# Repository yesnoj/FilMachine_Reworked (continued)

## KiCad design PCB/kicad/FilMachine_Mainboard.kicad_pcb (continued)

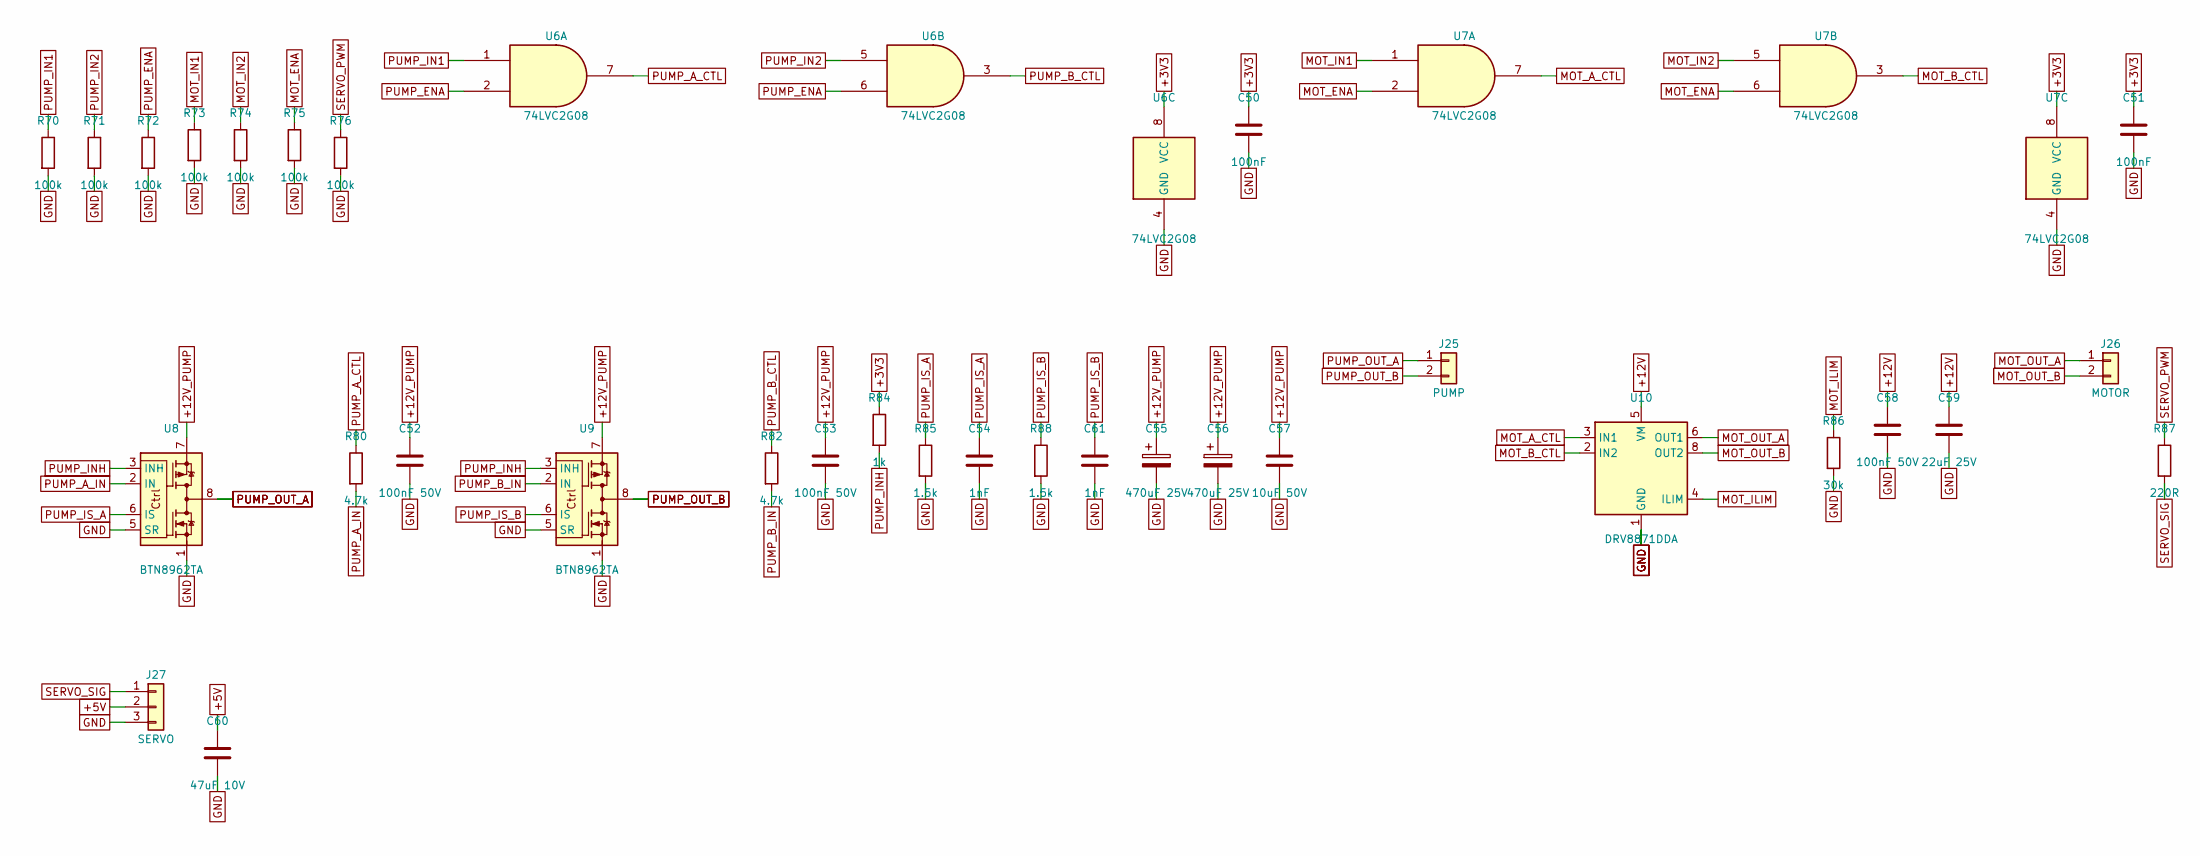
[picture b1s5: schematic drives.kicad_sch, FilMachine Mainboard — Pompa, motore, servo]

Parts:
C50, C51: 100nF; C_0603_1608Metric; MPN MLCC 100nF; LCSC C14663
C52, C53, C58: 100nF 50V; C_0805_2012Metric; MPN MLCC 100nF 50V; LCSC C49678
C54, C61: 1nF; C_0603_1608Metric; MPN MLCC 1nF; LCSC C1588
C55, C56: 470uF 25V; CP_Radial_D10.0mm_P5.00mm; MPN 25ZLH470MEFC10X12.5; LCSC C338188
C57: 10uF 50V; C_1206_3216Metric; MPN MLCC 10uF 50V; LCSC C13585
C59: 22uF 25V; C_1206_3216Metric; MPN MLCC 22uF 25V; LCSC C12891
C60: 47uF 10V; C_1206_3216Metric; MPN MLCC 47uF 10V; LCSC C96123
J25: PUMP; TB_WJ500V-5.08-2P; MPN WJ500V-5.08-2P; LCSC C8465
J26: MOTOR; TB_DB301V-3.5-2P; MPN DB301V-3.5-2P-GN-S; LCSC C695629
J27: SERVO; PinHeader_1x03_P2.54mm_Vertical; MPN PZ254V-11-03P; LCSC C2937625
R70, R71, R72, R73, R74, R75, R76: 100k; R_0603_1608Metric; MPN 0603 100k 1%; LCSC C25803
R80, R82: 4.7k; R_0603_1608Metric; MPN 0603 4.7k 1%; LCSC C23162
R84: 1k; R_0603_1608Metric; MPN 0603 1k 1%; LCSC C21190
R85, R88: 1.5k; R_0603_1608Metric; MPN 0603 1.5k 1%; LCSC C22843
R86: 30k; R_0603_1608Metric; MPN 0603 30k 1%; LCSC C22984
R87: 220R; R_0603_1608Metric; MPN 0603 220R 1%; LCSC C22962
U6, U7: 74LVC2G08; SSOP-8_2.95x2.8mm_P0.65mm; MPN SN74LVC2G08DCTR; LCSC C352973
U8, U9: BTN8962TA; TO-263-7_TabPin8; MPN BTN8962TAAUMA1; LCSC C112630
U10: DRV8871DDA; TI_SO-PowerPAD-8_ThermalVias; MPN DRV8871DDAR; LCSC C75864

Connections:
+3V3: C50.1, C51.1, R84.1, U6.8 (VCC), U7.8 (VCC); also elsewhere on the board
+5V: C60.1, J27.2; also elsewhere on the board
+12V: C58.1, C59.1, U10.5 (VM); also elsewhere on the board
+12V_PUMP: C52.1, C53.1, C55.1, C56.1, C57.1, U8.7, U9.7; also elsewhere on the board
GND: C50.2, C51.2, C52.2, C53.2, C54.2, C55.2, C56.2, C57.2, C58.2, C59.2, C60.2, C61.2, J27.3, R70.2, R71.2, R72.2, R73.2, R74.2, R75.2, R76.2, R85.2, R86.2, R88.2, U6.4 (GND), U7.4 (GND), U8.1, U8.5 (SR), U9.1, U9.5 (SR), U10.1 (GND), U10.7 (GND), U10.9 (GND); also elsewhere on the board
MOT_A_CTL: U7.7, U10.3 (IN1)
MOT_B_CTL: U7.3, U10.2 (IN2)
MOT_ENA: R75.1, U7.2, U7.6; also elsewhere on the board
MOT_ILIM: R86.1, U10.4 (ILIM)
MOT_IN1: R73.1, U7.1; also elsewhere on the board
MOT_IN2: R74.1, U7.5; also elsewhere on the board
MOT_OUT_A: J26.1, U10.6 (OUT1)
MOT_OUT_B: J26.2, U10.8 (OUT2)
PUMP_A_CTL: R80.1, U6.7
PUMP_A_IN: R80.2, U8.2 (IN)
PUMP_B_CTL: R82.1, U6.3
PUMP_B_IN: R82.2, U9.2 (IN)
PUMP_ENA: R72.1, U6.2, U6.6; also elsewhere on the board
PUMP_IN1: R70.1, U6.1; also elsewhere on the board
PUMP_IN2: R71.1, U6.5; also elsewhere on the board
PUMP_INH: R84.2, U8.3 (INH), U9.3 (INH)
PUMP_IS_A: C54.1, R85.1, U8.6 (IS); also elsewhere on the board
PUMP_IS_B: C61.1, R88.1, U9.6 (IS); also elsewhere on the board
PUMP_OUT_A: J25.1, U8.4, U8.8
PUMP_OUT_B: J25.2, U9.4, U9.8
SERVO_PWM: R76.1, R87.1; also elsewhere on the board
SERVO_SIG: J27.1, R87.2

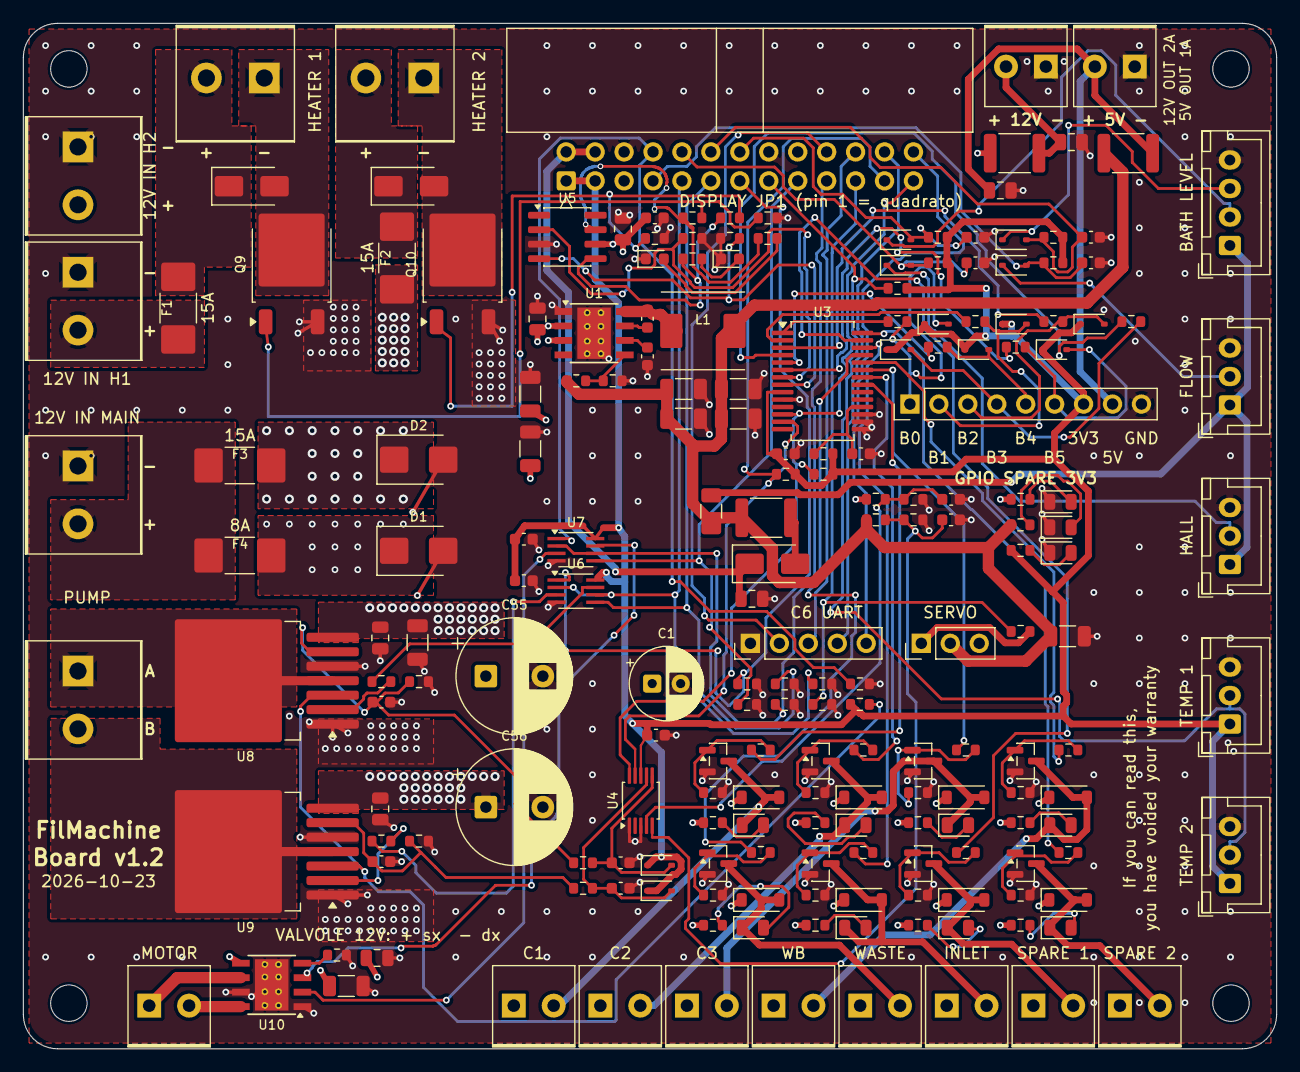
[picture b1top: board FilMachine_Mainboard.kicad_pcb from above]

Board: 4 copper layers, 110.0 x 90.0 mm, 205 parts (0 on the bottom side), 118 nets.

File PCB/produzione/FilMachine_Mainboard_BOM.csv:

Comment,Designator,Footprint,LCSC Part #
100uF 35V,C1,CP_Radial_D6.3mm_P2.50mm,C106694
10uF 50V,"C2,C3,C57",C_1206_3216Metric,C13585
220nF 50V,C4,C_0805_2012Metric,C5378
100nF,"C5,C13,C14,C15,C16,C17,C18,C19,C41,C50,C51",C_0603_1608Metric,C14663
1uF 50V,C6,C_0603_1608Metric,C15849
22uF 25V,"C7,C8,C9,C10,C59",C_1206_3216Metric,C12891
1nF,"C20,C21,C22,C23,C54,C61",C_0603_1608Metric,C1588
1uF 50V,C40,C_0805_2012Metric,C28323
100nF 50V,"C52,C53,C58",C_0805_2012Metric,C49678
470uF 25V,"C55,C56",CP_Radial_D10.0mm_P5.00mm,C338188
47uF 10V,C60,C_1206_3216Metric,C96123
10uF 25V,"C62,C63,C64",C_0805_2012Metric,C15850
SMBJ16A,"D1,D2",D_SMB,C19077571
Green,"D3,D4,D5",LED_0805_2012Metric,C2297
1N5819WS,"D6,D7,D10,D11,D12,D13,D47,D48,D49,D50,D51,D52",D_SOD-323,C191023
SS34,"D8,D41,D42",D_SMA,C8678
B5819W,"D21,D22,D23,D24,D25,D26,D27,D28",D_SOD-123,C8598
Yellow,"D31,D32,D33,D34,D35,D36,D37,D38",LED_0805_2012Metric,C2296
Red,"D43,D44",LED_0603_1608Metric,C2286
15A,"F1,F2,F3",FUSE_2410_SMD,C136393
8A,F4,FUSE_2410_SMD,C136390
1.1A,"F5,F7",Fuse_1812_4532Metric,C269134
0.5A,F6,Fuse_1206_3216Metric,C720075
2A,F8,Fuse_1812_4532Metric,C960026
12V IN HEATER 1 / 12V IN HEATER 2 / 12V IN MAIN / HEATER 1 / HEATER 2 / PUMP,"J1,J2,J3,J23,J24,J25",TB_WJ500V-5.08-2P,C8465
DISPLAY JP1,J5,IDC-Header_2x13_P2.54mm_Horizontal,C7430326
BATH LEVEL,J7,JST_XH_B4B-XH-A_1x04_P2.50mm_Vertical,C37815
FLOW / HALL / TEMP 1 / TEMP 2,"J11,J12,J13,J14",JST_XH_B3B-XH-A_1x03_P2.50mm_Vertical,C2316
SERVO,J27,PinHeader_1x03_P2.54mm_Vertical,C2937625
12V OUT / 5V OUT / MOTOR / SPARE OUT 1 / SPARE OUT 2 / VALVE C1 / VALVE C2 / VALVE C3 / VALVE INLET / VALVE WASTE / VALVE WB,"J15,J16,J17,J18,J19,J20,J21,J22,J26,J28,J29",TB_DB301V-3.5-2P,C695629
GPIO SPARE,J30,PinHeader_1x09_P2.54mm_Vertical,C492408
10uH,L1,L_SLO0630H,C207842
AO3400A,"Q1,Q2,Q3,Q4,Q5,Q6,Q7,Q8",SOT-23,C20917
AOD4184A,"Q9,Q10",TO-252-2,C99124
100k,"R1,R9,R41,R42,R43,R44,R45,R46,R47,R48,R61,R62,R70,R71,R72,R73,R74,R75,R76",R_0603_1608Metric,C25803
24k,R2,R_0603_1608Metric,C23352
4.7k,"R3,R16,R51,R52,R53,R54,R55,R56,R57,R58,R67,R68,R80,R82",R_0603_1608Metric,C23162
1k,"R4,R5,R84,R97,R98,R99,R100,R101,R102",R_0603_1608Metric,C21190
10k,"R8,R12,R13,R14,R20,R21,R22,R23,R64,R66",R_0603_1608Metric,C25804
15k,R10,R_0603_1608Metric,C22809
20k,R11,R_0603_1608Metric,C4184
100R,"R31,R32,R33,R34,R35,R36,R37,R38",R_0603_1608Metric,C22775
10R,"R63,R65",R_0603_1608Metric,C22859
1.5k,"R85,R88",R_0603_1608Metric,C22843
30k,R86,R_0603_1608Metric,C22984
220R,R87,R_0603_1608Metric,C22962
LMR33630ADDA,U1,TI_SO-PowerPAD-8_ThermalVias,C841384
MCP23017-E/SS,U3,SSOP-28_5.3x10.2mm_P0.65mm,C558584
ADS1115,U4,VSSOP-10_3x3mm_P0.5mm,C37593
UCC27524D,U5,SOIC-8_3.9x4.9mm_P1.27mm,C465729
74LVC2G08,"U6,U7",SSOP-8_2.95x2.8mm_P0.65mm,C352973
BTN8962TA,"U8,U9",TO-263-7_TabPin8,C112630
DRV8871DDA,U10,TI_SO-PowerPAD-8_ThermalVias,C75864

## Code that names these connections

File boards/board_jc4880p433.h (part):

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#define TOUCH_DRIVER_GT911          1
#define TOUCH_DRIVER_GT911_P4       1       /* Enables P4-specific coord remapping */

#define I2C_SDA                     7       /* Touch/peripheral I2C data */
#define I2C_SCL                     8       /* Touch/peripheral I2C clock */
#define TOUCH_INT_PIN               (-1)    /* GT911 interrupt (not wired) */
#define TOUCH_RST_PIN               (-1)    /* GT911 reset (not wired) */

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/* ═══════════════════════════════════════════════
 * Temperature — DS18B20 OneWire
 * ═══════════════════════════════════════════════ */
#define TEMPERATURE_BUS_PIN         35      /* OneWire data — JP1 pin 15 */
#define TEMPERATURE_SENSOR_BATH     0
#define TEMPERATURE_SENSOR_CHEMICAL 1

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 *
 * NOTE: Some DBH-12V variants use IN1/IN2 as direct PWM lines
 * (forward PWM on IN1, reverse PWM on IN2, EN=enable). If your
 * board works that way, swap PUMP_ENA_PIN with PUMP_IN1/IN2_PIN
 * and adjust pump_run() in accessories.c accordingly.
 *
 * Pins allocated from JP1 Expand IO header.
 * ═══════════════════════════════════════════════ */
#define HAS_PUMP_HBRIDGE            1
#define PUMP_IN1_PIN                49      /* JP1 pin 13 — pump direction A */
#define PUMP_IN2_PIN                50      /* JP1 pin 11 — pump direction B */
#define PUMP_ENA_PIN                51      /* JP1 pin 9  — pump PWM speed  */
#define PUMP_FLOW_ML_MIN            600     /* Kamoer KPHM600 at 100 % (12 V): 600 ml/min */

/* ═══════════════════════════════════════════════
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
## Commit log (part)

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2026-03-16 fix: drag & drop auto-scroll, save button, snprintf float display
    - Add proportional auto-scroll during step drag (speed based on distance from edge)
    - Fix Save button not activating after step reorder (prev pointer comparison)
    - Reset scroll position after dropping step to avoid stuck offset
    - Fix tolerance display showing 'f' (lv_snprintf → snprintf for float support)
    - Fix temperature display in checkup page (same snprintf workaround)
    - Move checkup UI strings to FilMachine.h defines
2026-03-16 feat: live reorder drag & drop with auto-scroll and snprintf fix
2026-03-17 Rework
2026-03-17 Small bug fixing
2026-03-17 Other small fixes
2026-03-17 Added button for close filter popup
2026-03-17 Drain Machine and Clean Machine added
2026-03-18 Added settings to Machine Settings page
2026-03-18 Sel-Checkup and some small fix to strings
2026-03-18 Added software update
2026-03-19 new automatic tests implemented
2026-03-19 Finished refactoring
2026-03-20 All UI component details ad centralized, for manage different resolution easly
2026-03-20 feat: dual-board support (JC4827W543 + Makerfabs), centralized UI profile fixes, sensor drivers, popup improvements - Add JC4827W543 board support: NV3041A QSPI display + GT911 touch (conditional ini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
2026-03-22 Small fixes
2026-03-22 Fixed step scroll
2026-03-22 Added alarms at end of Cleaning/Draining
2026-03-23 added support for board JC4880P433 (480×800)
2026-03-25 So many stuff reworked!
2026-03-26 Fixed random splash screen
2026-03-26 New random fonts
2026-03-26 Updated scripts
2026-03-27 Small bugfixes
2026-03-27 Added support for mobile application
2026-03-28 First Commit from Flutter app support
2026-03-29 Small fix on checkup page
2026-03-31 Fixing problems with WiFi and new board
2026-03-31 Wifi connection bugfix
2026-03-31 Small fixes of synchronization
2026-04-02 Fixed splash scren
2026-04-02 Wifi connection after the PLAY button is pressed.
2026-04-02 Fixed close buttons
2026-04-02 so many fixes, also graphical. this commit will solve FPS issue and discard changes on steps/process , and other small bugfix
2026-04-03 Synchronization fixes
2026-04-03 Updated README.md and other little things
2026-04-03 Removed support for unused boards.
2026-04-04 Board optimization
2026-04-06 Dimming logic changed + NVS storage for wifi credential
2026-04-06 Fixed pins on external 2x13 pin board
2026-04-06 Updated to LVGL 9.5.0
2026-04-06 Updated methods to 9.5
2026-05-02 Major upgrade: ESP32-P4 port, DBH-12V pump H-bridge, PCA9685 removed, new UI pages
2026-05-04 Updated pin layout
2026-05-04 Removed old reference to board not used
2026-05-04 Iconography for connections
2026-06-09 New component arrived!
2026-06-09 Fix PumpInvert switch
